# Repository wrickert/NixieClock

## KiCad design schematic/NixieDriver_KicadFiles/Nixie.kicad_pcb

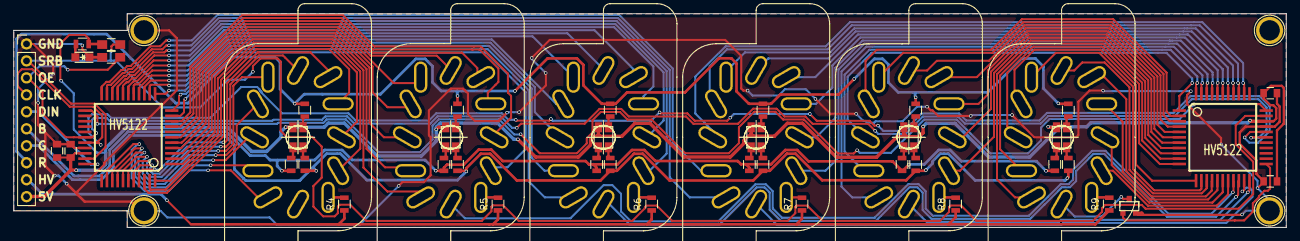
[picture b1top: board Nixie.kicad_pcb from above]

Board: 2 copper layers, 190.5 x 32.0 mm, 48 parts (0 on the bottom side), 102 nets.

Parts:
C6, C7: 100nF; C_0805
C8, C9: 10nF; C_0805
D1, D2, D3, D4, D6, D7: Led_RGB_CA; RGB_LED_CA
D5: LED; LED_0805
JP1: M10LOCK; Pin_Header_Straight_1x10_Pitch2.54mm
N1, N2, N3, N4, N5, N6: IN-12B; nixie_in12b_measured
Q1: FET; SparkFun-SOT23-3
R1, R10, R13, R16, R20, R23: 100R; R_0805
R2, R3, R11, R12, R14, R15, R17, R18, R19, R21, R22, R24, R25: 120R; R_0805
R4, R5, R6, R7, R8, R9: 1K5; R_0805
R26, R27: 10K; R_0805_HandSoldering
U2, U3: HV5122

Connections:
+5V: C6.1, C7.1, C8.1, C9.1, D1.1, D2.1, D3.1, D4.1, D6.1, D7.1, JP1.10, R18.2, R26.1, U2.31, U3.31
/1: N1.1, U2.35
/2: N1.2, U2.36
/3: N1.3, U2.37
/4: N1.4, U2.38
/5: N1.5, U2.39
/6: N1.6, U2.40
/7: N1.7, U2.41
/8: N1.8, U2.42
/9: N1.9, U2.43
/10: N1.0, U2.44
/11: N2.1, U2.1
/12: N2.2, U2.2
/13: N2.3, U2.3
/14: N2.4, U2.4
/15: N2.5, U2.5
/16: N2.6, U2.6
/17: N2.7, U2.7
/18: N2.8, U2.8
/19: N2.9, U2.9
/20: N2.0, U2.10
/21: N3.1, U2.11
/22: N3.2, U2.12
/23: N3.3, U2.13
/24: N3.4, U2.14
/25: N3.5, U2.15
/26: N3.6, U2.16
/27: N3.7, U2.17
/28: N3.8, U2.18
/29: N3.9, U2.19
/30: N3.0, U2.20
/31: N4.1, U2.21
/32: N4.2, U2.22
/33: N4.3, U3.35
/34: N4.4, U3.36
/35: N4.5, U3.37
/36: N4.6, U3.38
/37: N4.7, U3.39
/38: N4.8, U3.40
/39: N4.9, U3.41
/40: N4.0, U3.42
/41: N5.1, U3.43
/42: N5.2, U3.44
/43: N5.3, U3.1
/44: N5.4, U3.2
/45: N5.5, U3.3
/46: N5.6, U3.4
/47: N5.7, U3.5
/48: N5.8, U3.6
/49: N5.9, U3.7
/50: N5.0, U3.8
/51: N6.1, U3.9
/52: N6.2, U3.10
/53: N6.3, U3.11
/54: N6.4, U3.12
/55: N6.5, U3.13
/56: N6.6, U3.14
/57: N6.7, U3.15
/58: N6.8, U3.16
/59: N6.9, U3.17
/60: N6.0, U3.18
/B: JP1.6, R3.2, R12.2, R15.2, R19.2, R22.2, R25.2
/CLK: JP1.4, U2.29, U3.29
/DIN: JP1.5, U2.33
/DP1: N2.LHDP, U3.19
/DP2: N3.LHDP, U3.20
/DP3: N4.LHDP, U3.21
/DP4: N5.LHDP, U3.22
/DP5: N6.LHDP, Q1.3
/G: JP1.7, R2.2, R11.2, R14.2, R17.2, R21.2, R24.2
/OE: JP1.3, R27.1, U2.28, U3.28
/R: JP1.8, R1.2, R10.2, R13.2, R16.2, R20.2, R23.2
/SRB: JP1.2, R26.2, U2.32, U3.32
GND: C6.2, C7.2, C8.2, C9.2, D5.1, JP1.1, Q1.2, R27.2, U2.30, U3.30
unnamed: D1.2, R1.1
unnamed: D1.3, R2.1
unnamed: D1.4, R3.1
unnamed: D2.2, R10.1
unnamed: D2.3, R11.1
unnamed: D2.4, R12.1
unnamed: D3.2, R13.1
unnamed: D3.3, R14.1
unnamed: D3.4, R15.1
unnamed: D4.2, R16.1
unnamed: D4.3, R17.1
unnamed: D4.4, R19.1
unnamed: D5.2, R18.1
unnamed: D6.2, R20.1
unnamed: D6.3, R21.1
unnamed: D6.4, R22.1
unnamed: D7.2, R23.1
unnamed: D7.3, R24.1
unnamed: D7.4, R25.1
unnamed: N1.A, R4.2
unnamed: N2.A, R5.2
unnamed: N3.A, R6.2
unnamed: N4.A, R7.2
unnamed: N5.A, R8.2
unnamed: N6.A, R9.2
unnamed: Q1.1, U3.23
unnamed: U2.23, U3.33
VPP: JP1.9, R4.1, R5.1, R6.1, R7.1, R8.1, R9.1

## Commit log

2018-07-15 first commit - partial schematic
2018-07-16 Small changes
2019-07-17 Bring Github up to date
